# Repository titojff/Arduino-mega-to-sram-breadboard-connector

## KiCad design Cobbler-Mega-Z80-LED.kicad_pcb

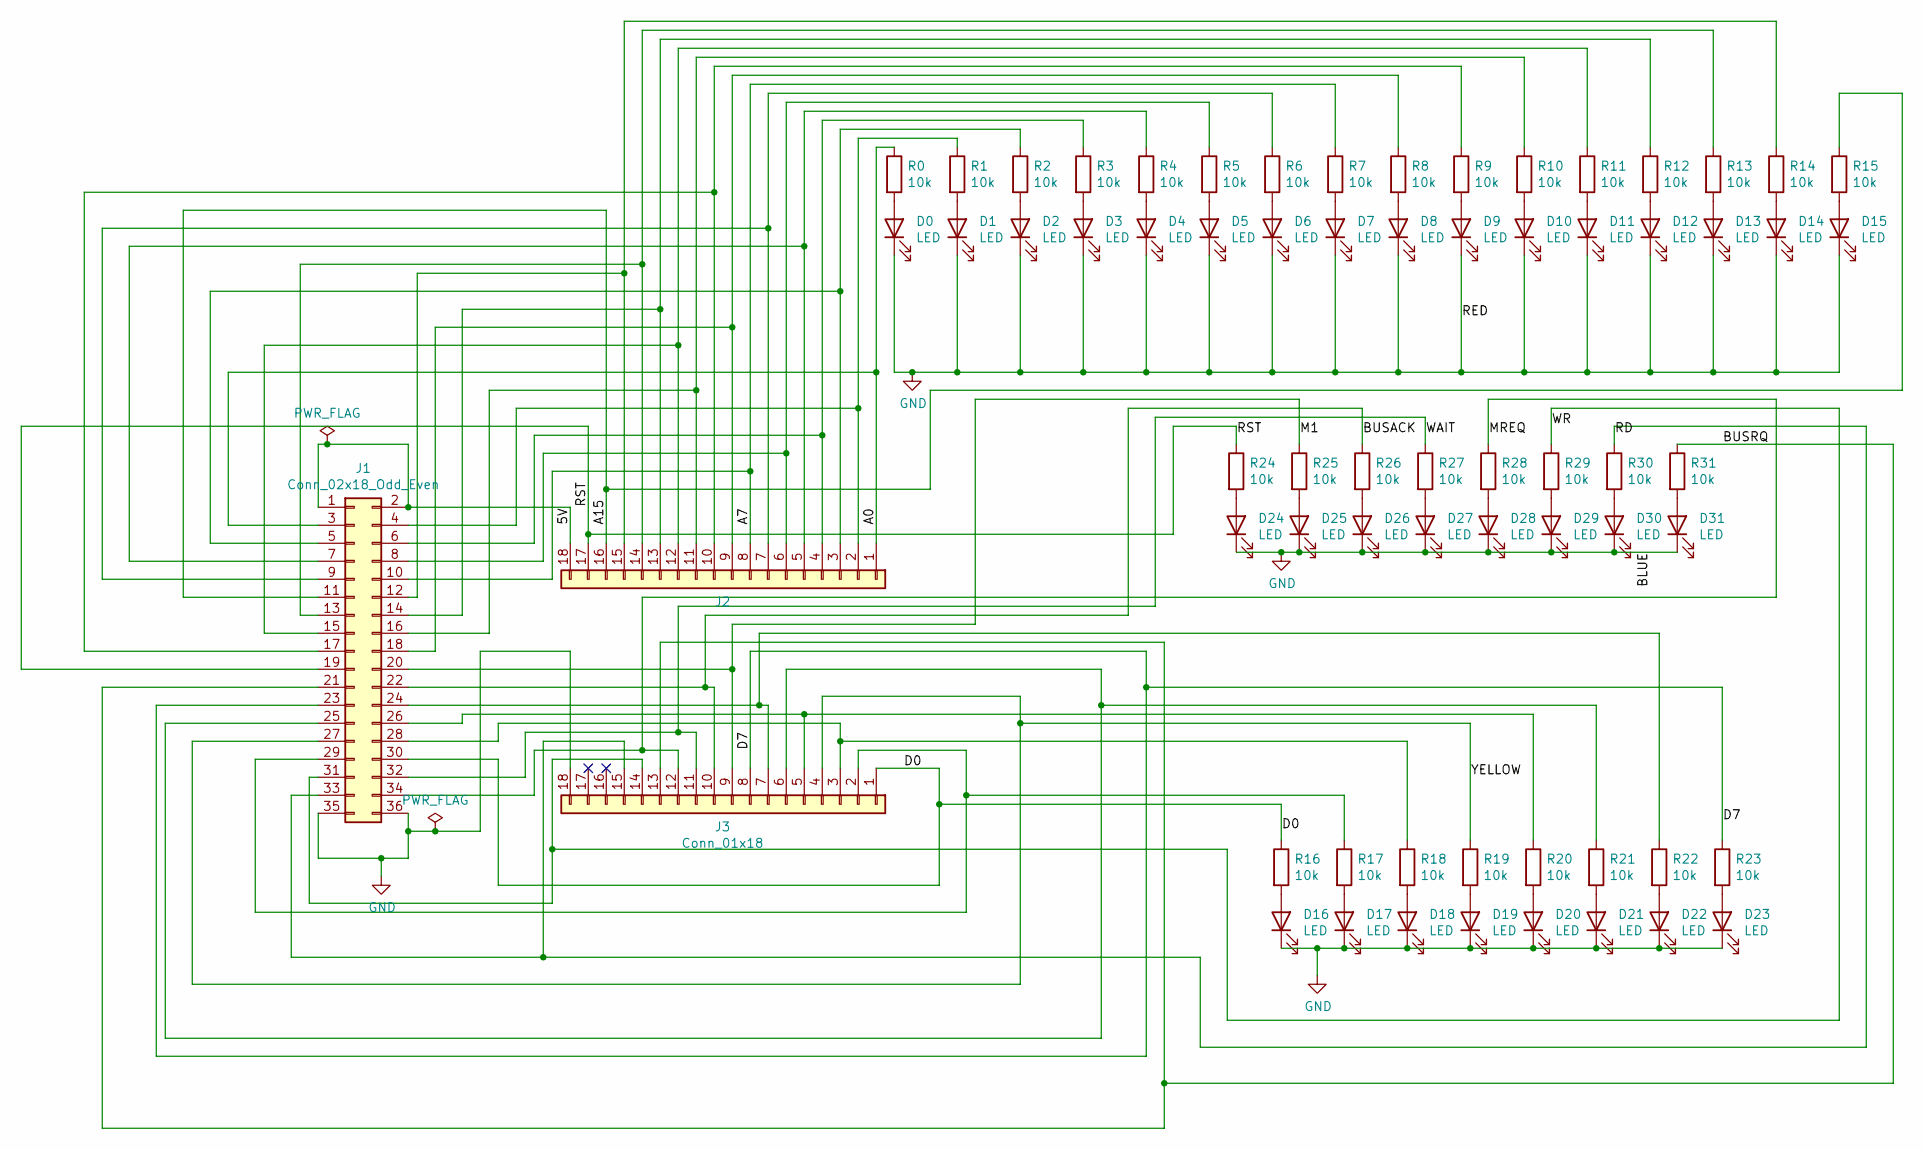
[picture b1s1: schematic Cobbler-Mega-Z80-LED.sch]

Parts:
D0, D1, D2, D3, D4, D5, D6, D7, D8, D9, D10, D11, D12, D13, D14, D15, D16, D17, D18, D19, D20, D21, D22, D23, D24, D25, D26, D27, D28, D29, D30, D31: LED; LED_0603_1608Metric
J1: Conn_02x18_Odd_Even; PinHeader_2x18_P2.54mm_Vertical
J2: Cn18; PinHeader_1x18_P2.54mm_Vertical
J3: Conn_01x18; PinHeader_1x18_P2.54mm_Vertical
R0, R1, R2, R3, R4, R5, R6, R7, R8, R9, R10, R11, R12, R13, R14, R15, R16, R17, R18, R19, R20, R21, R22, R23, R24, R25, R26, R27, R28, R29, R30, R31: 10k; R_0805_2012Metric

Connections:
/5V: J1.1, J1.2, J2.18
/A0: J1.3, J2.1, R0.1
/A7: J1.10, J2.8, R7.1
/A15: J1.11, J2.16, R15.1
/BUSACK: J1.22, J3.10, R26.1
/BUSRQ: J1.21, J3.13, R31.1
/D0: J1.30, J3.1, R16.1
/D7: J1.23, J3.8, R23.1
/M1: J1.20, J3.9, R25.1
/MREQ: J1.34, J3.12, R28.1
/RD: J1.33, J3.15, R30.1
/RST: J1.19, J2.17, R24.1
/WAIT: J1.32, J3.11, R27.1
/WR: J1.31, J3.14, R29.1
/YELLOW: J1.27, J3.4, R19.1
GND: D0.1 (K), D1.1 (K), D2.1 (K), D3.1 (K), D4.1 (K), D5.1 (K), D6.1 (K), D7.1 (K), D8.1 (K), D9.1 (K), D10.1 (K), D11.1 (K), D12.1 (K), D13.1 (K), D14.1 (K), D15.1 (K), D16.1 (K), D17.1 (K), D18.1 (K), D19.1 (K), D20.1 (K), D21.1 (K), D22.1 (K), D23.1 (K), D24.1 (K), D25.1 (K), D26.1 (K), D27.1 (K), D28.1 (K), D29.1 (K), D30.1 (K), D31.1 (K), J1.35, J1.36, J3.18
unnamed: D0.2 (A), R0.2
unnamed: D1.2 (A), R1.2
unnamed: D2.2 (A), R2.2
unnamed: D3.2 (A), R3.2
unnamed: D4.2 (A), R4.2
unnamed: D5.2 (A), R5.2
unnamed: D6.2 (A), R6.2
unnamed: D7.2 (A), R7.2
unnamed: D8.2 (A), R8.2
unnamed: D9.2 (A), R9.2
unnamed: D10.2 (A), R10.2
unnamed: D11.2 (A), R11.2
unnamed: D12.2 (A), R12.2
unnamed: D13.2 (A), R13.2
unnamed: D14.2 (A), R14.2
unnamed: D15.2 (A), R15.2
unnamed: D16.2 (A), R16.2
unnamed: D17.2 (A), R17.2
unnamed: D18.2 (A), R18.2
unnamed: D19.2 (A), R19.2
unnamed: D20.2 (A), R20.2
unnamed: D21.2 (A), R21.2
unnamed: D22.2 (A), R22.2
unnamed: D23.2 (A), R23.2
unnamed: D24.2 (A), R24.2
unnamed: D25.2 (A), R25.2
unnamed: D26.2 (A), R26.2
unnamed: D27.2 (A), R27.2
unnamed: D28.2 (A), R28.2
unnamed: D29.2 (A), R29.2
unnamed: D30.2 (A), R30.2
unnamed: D31.2 (A), R31.2
unnamed: J1.4, J2.2, R1.1
unnamed: J1.5, J2.3, R2.1
unnamed: J1.6, J2.4, R3.1
unnamed: J1.7, J2.5, R4.1
unnamed: J1.8, J2.6, R5.1
unnamed: J1.9, J2.7, R6.1
unnamed: J1.12, J2.15, R14.1
unnamed: J1.13, J2.14, R13.1
unnamed: J1.14, J2.13, R12.1
unnamed: J1.15, J2.12, R11.1
unnamed: J1.16, J2.11, R10.1
unnamed: J1.17, J2.10, R9.1
unnamed: J1.18, J2.9, R8.1
unnamed: J1.24, J3.7, R22.1
unnamed: J1.25, J3.6, R21.1
unnamed: J1.26, J3.5, R20.1
unnamed: J1.28, J3.3, R18.1
unnamed: J1.29, J3.2, R17.1

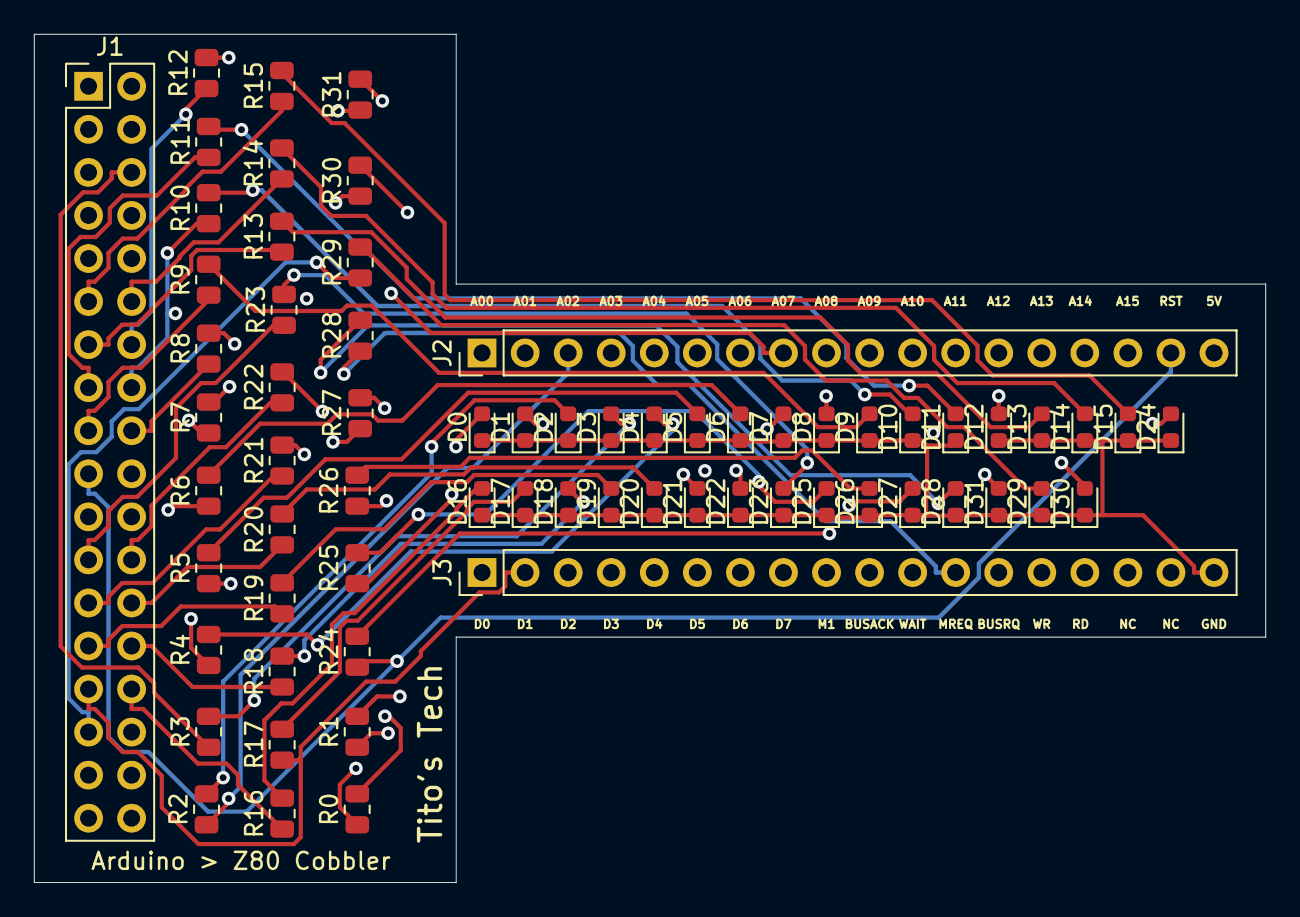
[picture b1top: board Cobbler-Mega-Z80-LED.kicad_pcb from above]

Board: 4 copper layers, 72.6 x 50.0 mm, 67 parts (0 on the bottom side), 66 nets.
